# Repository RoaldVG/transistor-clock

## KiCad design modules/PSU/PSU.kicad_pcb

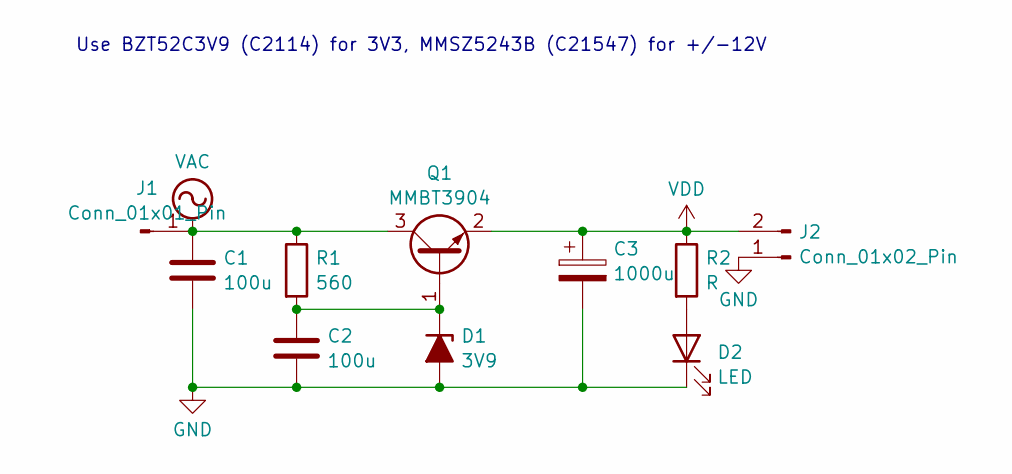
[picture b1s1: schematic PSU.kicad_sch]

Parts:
C1, C2: 100u; CP_EIA-3528-12_Kemet-T; LCSC Part # C16133
C3: 1000u; CP_Elec_10x10.5; LCSC Part # C3359
D1: 3V9; D_SOD-123; LCSC Part # C2114
D2: LED; LED_0603_1608Metric
J1: Conn_01x01_Pin; PinHeader_1x01_P2.54mm_Vertical
J2: Conn_01x02_Pin; PinHeader_1x02_P2.54mm_Vertical
Q1: MMBT3904; SOT-23; LCSC Part # C20526v
R1: 560; R_0603_1608Metric; LCSC Part # C23204
R2: R; R_0603_1608Metric

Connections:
GND: C1.2, C2.1, C3.2, D1.2 (A), D2.1 (K), J2.1
unnamed: C2.2, D1.1 (K), Q1.1 (B), R1.2
unnamed: D2.2 (A), R2.2
VAC: C1.1, J1.1, Q1.3 (C), R1.1
VDD: C3.1, J2.2, Q1.2 (E), R2.1

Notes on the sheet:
Use BZT52C3V9 (C2114) for 3V3, MMSZ5243B (C21547) for +/-12V

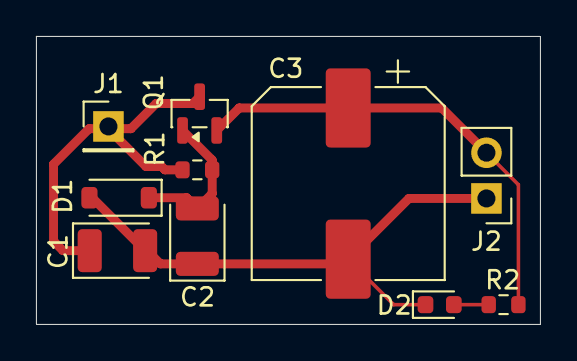
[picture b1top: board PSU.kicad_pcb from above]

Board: 2 copper layers, 28.0 x 16.0 mm, 10 parts (0 on the bottom side), 5 nets.

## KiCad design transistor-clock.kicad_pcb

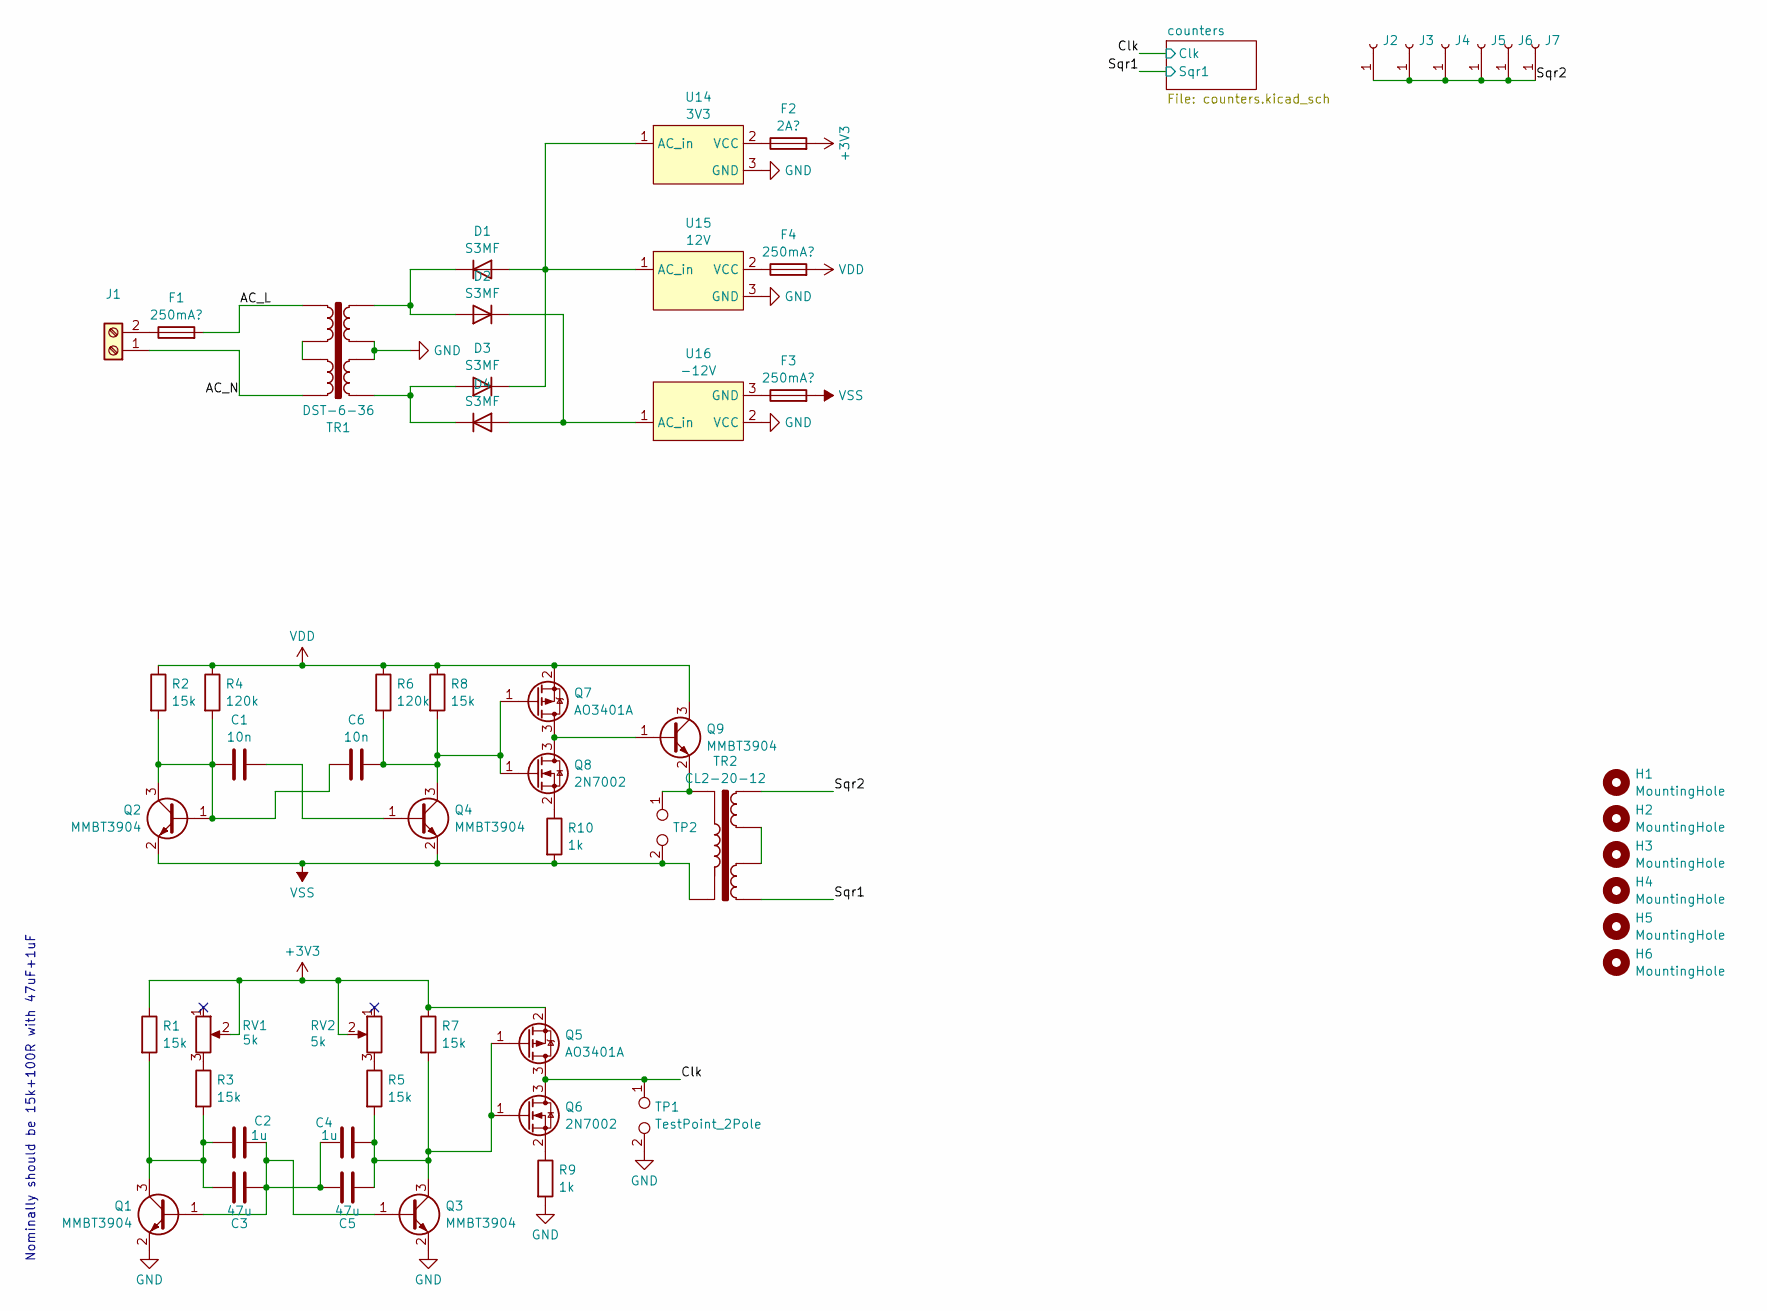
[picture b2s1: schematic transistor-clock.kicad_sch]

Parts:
C1, C6: 10n; C_0603_1608Metric; LCSC Part # C57112
C2, C4: 1u; C_0603_1608Metric; LCSC Part # C15849
C3, C5: 47u; C_0805_2012Metric; LCSC Part # C16780
D1, D2, D3, D4: S3MF; D_SMA; LCSC Part # C64874
F1, F3, F4: 250mA?; Fuse_Littelfuse-NANO2-885; LCSC Part # C41371860
F2: 2A?; Fuse_Littelfuse-NANO2-885; LCSC Part # C41371860
H1, H2, H3, H4, H5, H6: MountingHole; MountingHole_4.3mm_M4_DIN965
J1: Screw_Terminal_01x02; TerminalBlock_MaiXu_MX126-5.0-02P_1x02_P5.00mm
J2, J3, J4, J5, J6, J7: Conn_01x01_Socket; PinHeader_1x01_P2.54mm_Vertical
Q1, Q2, Q3, Q4, Q9: MMBT3904; SOT-23; LCSC Part # C20526v
Q5, Q7: AO3401A; SOT-23; LCSC Part # C15127
Q6, Q8: 2N7002; SOT-23; LCSC Part # C8545
R1, R2, R3, R5, R7, R8: 15k; R_0603_1608Metric; LCSC Part # C22809
R4, R6: 120k; R_0603_1608Metric; LCSC Part # C25808
R9, R10: 1k; R_0603_1608Metric; LCSC Part # C21190
RV1, RV2: 5k; Potentiometer_Bourns_3214J_Horizontal; LCSC Part # C58391
TP1, TP2: TestPoint_2Pole; PinHeader_1x02_P2.54mm_Vertical
TR1: DST-6-36
TR2: CL2-20-12
U14: 3V3; module_PSU
U15: 12V; module_PSU
U16: -12V; module_PSU

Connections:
+3V3: F2.2, Q5.2 (S), R1.1, R7.1, RV1.2, RV2.2; also elsewhere on the board
/AC_L: F1.2, TR1.4
/AC_N: J1.1, TR1.1
/Clk: Q5.3 (D), Q6.3 (D), TP1.1; also elsewhere on the board
/Sqr1: TR2.1; also elsewhere on the board
/Sqr2: J2.1, J3.1, J4.1, J5.1, J6.1, J7.1, TR2.6
GND: Q1.2 (E), Q3.2 (E), R9.2, TP1.2, TR1.6, TR1.7, U14.3 (GND), U15.3 (GND), U16.2 (VCC); also elsewhere on the board
unnamed: D1.2 (A), D3.1 (K), U14.1 (AC_in), U15.1 (AC_in)
unnamed: D1.1 (K), D2.2 (A), TR1.5
unnamed: D2.1 (K), D4.2 (A), U16.1 (AC_in)
unnamed: D3.2 (A), D4.1 (K), TR1.8
unnamed: F1.1, J1.2
unnamed: C2.2, C3.2, C4.1, C5.1, Q1.1 (B), Q3.1 (B)
unnamed: C2.1, C3.1, Q1.3 (C), R1.2, R3.2
unnamed: C1.1, C6.1, Q2.1 (B), Q2.3 (C), R2.2, R4.2
unnamed: C4.2, C5.2, Q3.3 (C), Q5.1 (G), Q6.1 (G), R5.2, R7.2
unnamed: C1.2, Q4.1 (B)
unnamed: C6.2, Q4.3 (C), Q7.1 (G), Q8.1 (G), R6.2, R8.2
unnamed: Q6.2 (S), R9.1
unnamed: Q7.3 (D), Q8.3 (D), Q9.1 (B)
unnamed: Q8.2 (S), R10.1
unnamed: Q9.2 (E), TP2.1, TR2.12
unnamed: R3.1, RV1.3
unnamed: R5.1, RV2.3
unnamed: TR1.2, TR1.3
unnamed: TR2.3, TR2.4
unnamed: F2.1, U14.2 (VCC)
unnamed: F4.1, U15.2 (VCC)
unnamed: F3.1, U16.3 (GND)
VDD: F4.2, Q7.2 (S), Q9.3 (C), R2.1, R4.1, R6.1, R8.1
VSS: F3.2, Q2.2 (E), Q4.2 (E), R10.2, TP2.2, TR2.7

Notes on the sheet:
Nominally should be 15k+100R with 47uF+1uF

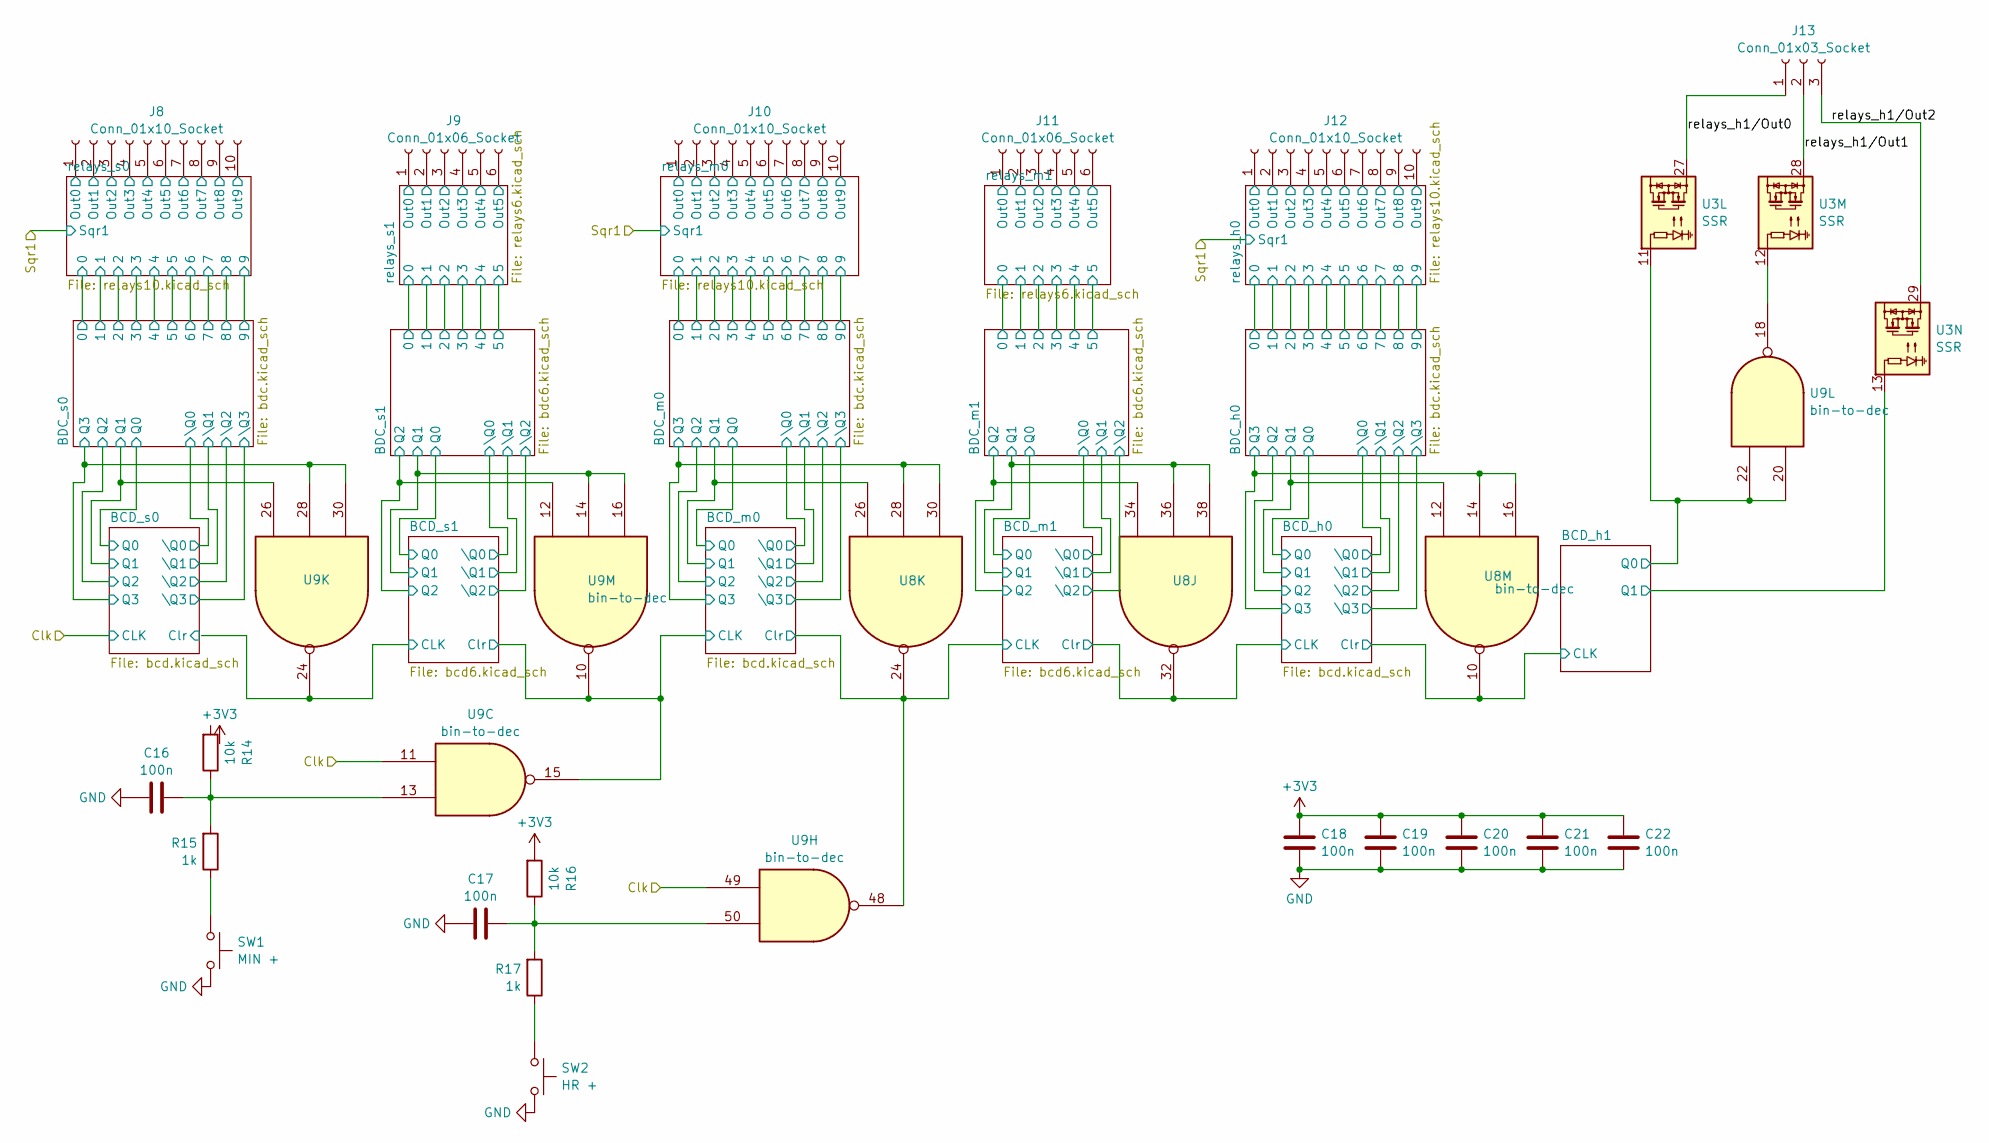
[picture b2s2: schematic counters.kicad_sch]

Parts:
C16, C17, C18, C19, C20, C21, C22: 100n; C_0603_1608Metric; LCSC Part # C14663
J8, J10, J12: Conn_01x10_Socket; PinHeader_1x10_P2.54mm_Vertical
J9, J11: Conn_01x06_Socket; PinHeader_1x06_P2.54mm_Vertical
J13: Conn_01x03_Socket; PinHeader_1x03_P2.54mm_Vertical
R14, R16: 10k; R_0603_1608Metric; LCSC Part # C25804
R15, R17: 1k; R_0603_1608Metric; LCSC Part # C21190
SW1: MIN +; SW_SPST_EVQPE1; LCSC Part # C720477
SW2: HR +; SW_SPST_EVQPE1; LCSC Part # C720477
U3: SSR; module_ssr
U8, U9: bin-to-dec; module_bdc_mpcie; LCSC Part # C185937

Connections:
+3V3: C18.1, C19.1, C20.1, C21.1, C22.1, R16.2, U8.24, U8.32, U9.10, U9.15, U9.24, U9.48; also elsewhere on the board
/Clk: U9.11, U9.49; also elsewhere on the board
/counters/BCD_h0/Clr: U8.10; also elsewhere on the board
/counters/BCD_h0/Q1: U8.12; also elsewhere on the board
/counters/BCD_h0/Q3: U8.14, U8.16; also elsewhere on the board
/counters/BCD_h1/Clr: U3.13; also elsewhere on the board
/counters/BCD_h1/Q0: U3.11, U9.20, U9.22; also elsewhere on the board
/counters/BCD_m0/Q1: U8.26; also elsewhere on the board
/counters/BCD_m0/Q3: U8.28, U8.30; also elsewhere on the board
/counters/BCD_m1/Q1: U8.36, U8.38; also elsewhere on the board
/counters/BCD_m1/Q2: U8.34; also elsewhere on the board
/counters/BCD_s0/Q1: U9.26; also elsewhere on the board
/counters/BCD_s0/Q3: U9.28, U9.30; also elsewhere on the board
/counters/BCD_s1/Q1: U9.14, U9.16; also elsewhere on the board
/counters/BCD_s1/Q2: U9.12; also elsewhere on the board
/counters/relays_h0/Out0: J12.1; also elsewhere on the board
/counters/relays_h0/Out1: J12.2; also elsewhere on the board
/counters/relays_h0/Out2: J12.3; also elsewhere on the board
/counters/relays_h0/Out3: J12.4; also elsewhere on the board
/counters/relays_h0/Out4: J12.5; also elsewhere on the board
/counters/relays_h0/Out5: J12.6; also elsewhere on the board
/counters/relays_h0/Out6: J12.7; also elsewhere on the board
/counters/relays_h0/Out7: J12.8; also elsewhere on the board
/counters/relays_h0/Out8: J12.9; also elsewhere on the board
/counters/relays_h0/Out9: J12.10; also elsewhere on the board
/counters/relays_h1/Out0: J13.1, U3.27
/counters/relays_h1/Out1: J13.2, U3.28
/counters/relays_h1/Out2: J13.3, U3.29
/counters/relays_m0/Out0: J10.1; also elsewhere on the board
/counters/relays_m0/Out1: J10.2; also elsewhere on the board
/counters/relays_m0/Out2: J10.3; also elsewhere on the board
/counters/relays_m0/Out3: J10.4; also elsewhere on the board
/counters/relays_m0/Out4: J10.5; also elsewhere on the board
/counters/relays_m0/Out5: J10.6; also elsewhere on the board
/counters/relays_m0/Out6: J10.7; also elsewhere on the board
/counters/relays_m0/Out7: J10.8; also elsewhere on the board
/counters/relays_m0/Out8: J10.9; also elsewhere on the board
/counters/relays_m0/Out9: J10.10; also elsewhere on the board
/counters/relays_m1/Out0: J11.1; also elsewhere on the board
/counters/relays_m1/Out1: J11.2; also elsewhere on the board
/counters/relays_m1/Out2: J11.3; also elsewhere on the board
/counters/relays_m1/Out3: J11.4; also elsewhere on the board
/counters/relays_m1/Out4: J11.5; also elsewhere on the board
/counters/relays_m1/Out5: J11.6; also elsewhere on the board
/counters/relays_s0/Out0: J8.1; also elsewhere on the board
/counters/relays_s0/Out1: J8.2; also elsewhere on the board
/counters/relays_s0/Out2: J8.3; also elsewhere on the board
/counters/relays_s0/Out3: J8.4; also elsewhere on the board
/counters/relays_s0/Out4: J8.5; also elsewhere on the board
/counters/relays_s0/Out5: J8.6; also elsewhere on the board
/counters/relays_s0/Out6: J8.7; also elsewhere on the board
/counters/relays_s0/Out7: J8.8; also elsewhere on the board
/counters/relays_s0/Out8: J8.9; also elsewhere on the board
/counters/relays_s0/Out9: J8.10; also elsewhere on the board
/counters/relays_s1/Out0: J9.1; also elsewhere on the board
/counters/relays_s1/Out1: J9.2; also elsewhere on the board
/counters/relays_s1/Out2: J9.3; also elsewhere on the board
/counters/relays_s1/Out3: J9.4; also elsewhere on the board
/counters/relays_s1/Out4: J9.5; also elsewhere on the board
/counters/relays_s1/Out5: J9.6; also elsewhere on the board
GND: C16.2, C17.2, C18.2, C19.2, C20.2, C21.2, C22.2, SW1.1, SW2.1; also elsewhere on the board
unnamed: C16.1, R14.1, R15.2, U9.13
unnamed: C17.1, R16.1, R17.2, U9.50
unnamed: R15.1, SW1.2
unnamed: R17.1, SW2.2
unnamed: U3.12, U9.18

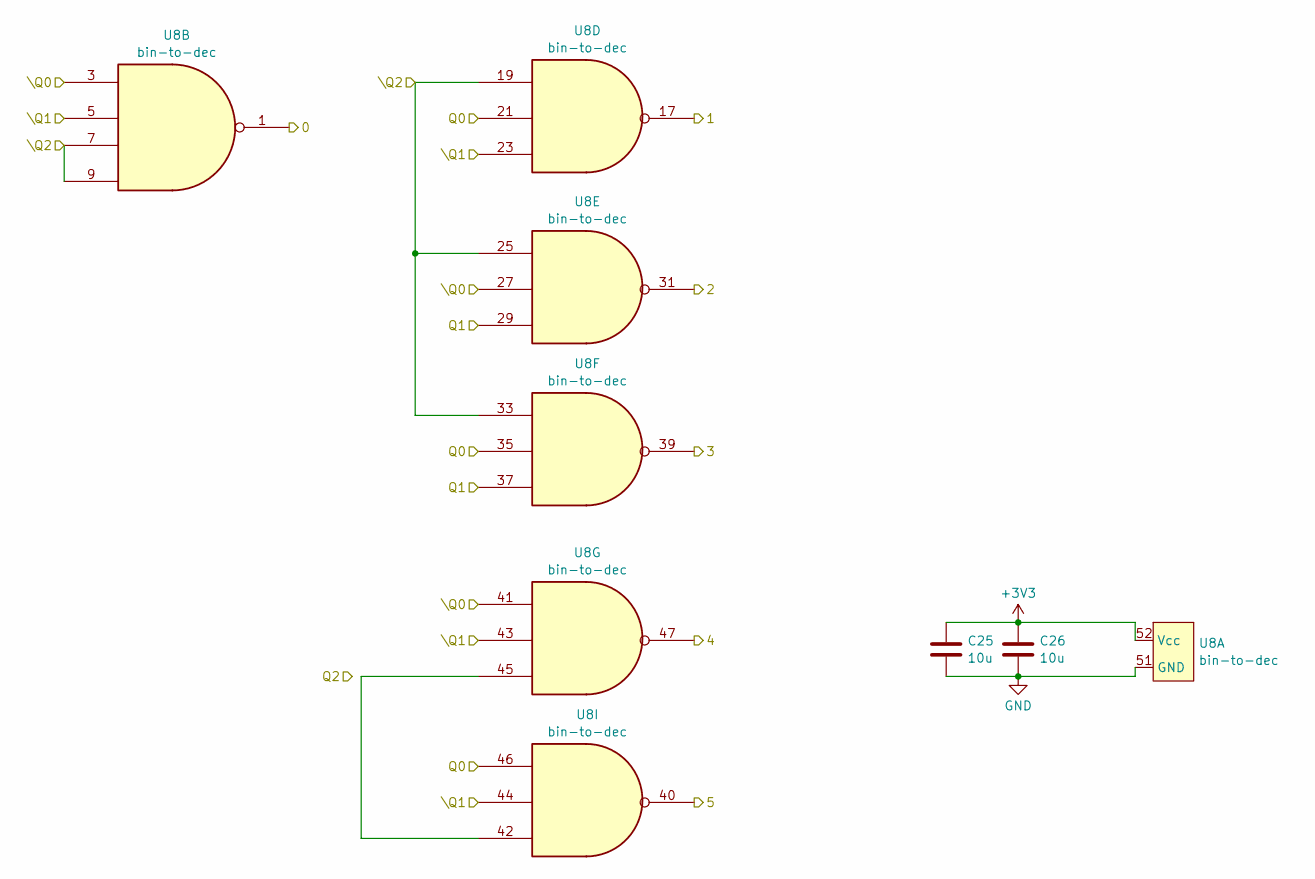
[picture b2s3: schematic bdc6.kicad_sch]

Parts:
C25, C26: 10u; C_0603_1608Metric; LCSC Part # C19702
U8: bin-to-dec; module_bdc_mpcie; LCSC Part # C185937

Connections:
+3V3: C25.1, C26.1, U8.52 (Vcc); also elsewhere on the board
/counters/BCD_m1/Q0: U8.21, U8.35, U8.46; also elsewhere on the board
/counters/BCD_m1/Q1: U8.29, U8.37; also elsewhere on the board
/counters/BCD_m1/\Q0: U8.3, U8.27, U8.41; also elsewhere on the board
/counters/BCD_m1/\Q1: U8.5, U8.23, U8.43, U8.44; also elsewhere on the board
/counters/BCD_m1/\Q2: U8.7, U8.9, U8.19, U8.25, U8.33; also elsewhere on the board
/counters/BDC_m1/0: U8.1; also elsewhere on the board
/counters/BDC_m1/1: U8.17; also elsewhere on the board
/counters/BDC_m1/2: U8.31; also elsewhere on the board
/counters/BDC_m1/3: U8.39; also elsewhere on the board
/counters/BDC_m1/4: U8.47; also elsewhere on the board
/counters/BDC_m1/5: U8.40; also elsewhere on the board
GND: C25.2, C26.2, U8.51 (GND); also elsewhere on the board
unnamed: U8.42, U8.45

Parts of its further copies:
C31, C32: 10u; C_0603_1608Metric; LCSC Part # C19702

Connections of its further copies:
+3V3: C31.1, C32.1; also elsewhere on the board
GND: C31.2, C32.2; also elsewhere on the board

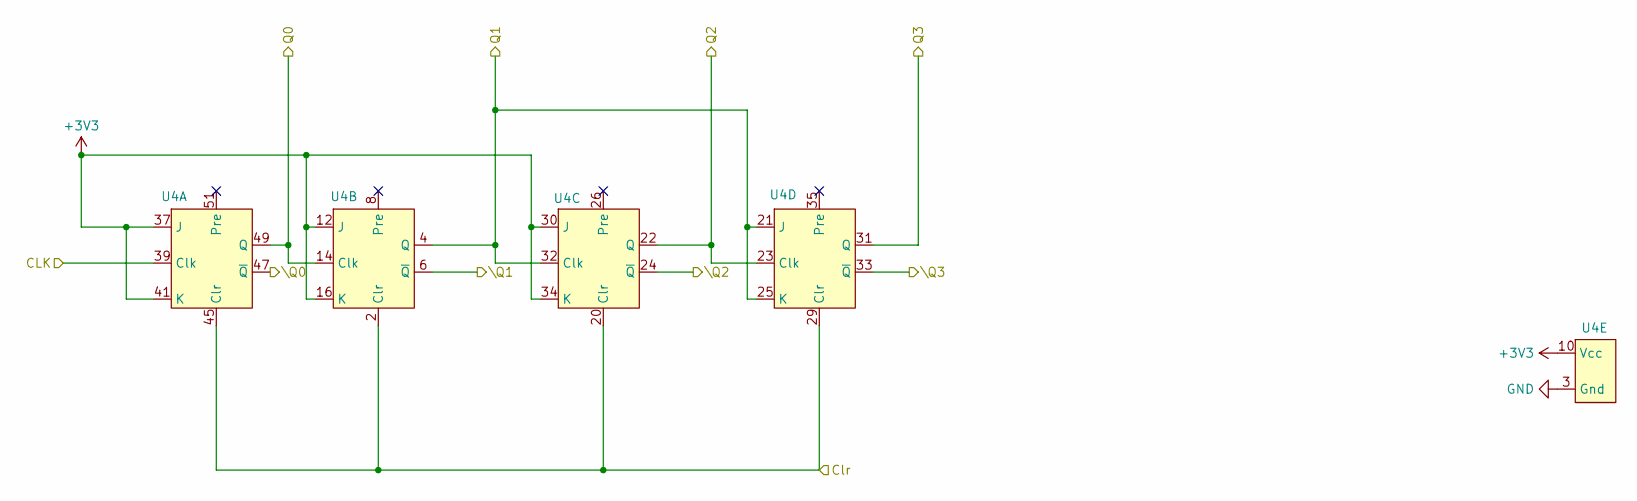
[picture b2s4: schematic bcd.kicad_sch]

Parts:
U4: flipflop; module_flipflop_mpcie; LCSC Part # C185937

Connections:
+3V3: U4.10 (Vcc), U4.12 (J), U4.16 (K), U4.18 (Vcc), U4.28 (Vcc), U4.30 (J), U4.34 (K), U4.36 (Vcc), U4.37 (J), U4.39 (Clk), U4.41 (K), U4.46 (Vcc); also elsewhere on the board
/counters/BCD_h0/Clr: U4.2 (Clr), U4.20 (Clr), U4.29 (Clr), U4.45 (Clr); also elsewhere on the board
/counters/BCD_h0/Q0: U4.14 (Clk), U4.49 (Q); also elsewhere on the board
/counters/BCD_h0/Q1: U4.4 (Q), U4.21 (J), U4.25 (K), U4.32 (Clk); also elsewhere on the board
/counters/BCD_h0/Q2: U4.22 (Q), U4.23 (Clk); also elsewhere on the board
/counters/BCD_h0/Q3: U4.31 (Q); also elsewhere on the board
/counters/BCD_h0/\Q0: U4.47 (~Q); also elsewhere on the board
/counters/BCD_h0/\Q1: U4.6 (~Q); also elsewhere on the board
/counters/BCD_h0/\Q2: U4.24 (~Q); also elsewhere on the board
/counters/BCD_h0/\Q3: U4.33 (~Q); also elsewhere on the board
GND: U4.3 (Gnd), U4.9 (Gnd), U4.19 (Gnd), U4.27 (Gnd), U4.43 (Gnd); also elsewhere on the board

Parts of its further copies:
U7, U10: flipflop; module_flipflop_mpcie; LCSC Part # C185937

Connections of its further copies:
+3V3: U7.10 (Vcc), U7.12 (J), U7.16 (K), U7.18 (Vcc), U7.28 (Vcc), U7.30 (J), U7.34 (K), U7.36 (Vcc), U7.37 (J), U7.41 (K), U7.46 (Vcc), U10.2 (Clr), U10.10 (Vcc), U10.12 (J), U10.16 (K), U10.18 (Vcc), U10.20 (Clr), U10.28 (Vcc), U10.29 (Clr), U10.30 (J), U10.34 (K), U10.36 (Vcc), U10.37 (J), U10.39 (Clk), U10.41 (K), U10.45 (Clr), U10.46 (Vcc); also elsewhere on the board
/Clk: U7.39 (Clk); also elsewhere on the board
/counters/BCD_m0/Q0: U10.14 (Clk), U10.49 (Q); also elsewhere on the board
/counters/BCD_m0/Q1: U10.4 (Q), U10.21 (J), U10.25 (K), U10.32 (Clk); also elsewhere on the board
/counters/BCD_m0/Q2: U10.22 (Q), U10.23 (Clk); also elsewhere on the board
/counters/BCD_m0/Q3: U10.31 (Q); also elsewhere on the board
/counters/BCD_m0/\Q0: U10.47 (~Q); also elsewhere on the board
/counters/BCD_m0/\Q1: U10.6 (~Q); also elsewhere on the board
/counters/BCD_m0/\Q2: U10.24 (~Q); also elsewhere on the board
/counters/BCD_m0/\Q3: U10.33 (~Q); also elsewhere on the board
/counters/BCD_s0/Clr: U7.2 (Clr), U7.20 (Clr), U7.29 (Clr), U7.45 (Clr)
/counters/BCD_s0/Q0: U7.14 (Clk), U7.49 (Q); also elsewhere on the board
/counters/BCD_s0/Q1: U7.4 (Q), U7.21 (J), U7.25 (K), U7.32 (Clk); also elsewhere on the board
/counters/BCD_s0/Q2: U7.22 (Q), U7.23 (Clk); also elsewhere on the board
/counters/BCD_s0/Q3: U7.31 (Q); also elsewhere on the board
/counters/BCD_s0/\Q0: U7.47 (~Q); also elsewhere on the board
/counters/BCD_s0/\Q1: U7.6 (~Q); also elsewhere on the board
/counters/BCD_s0/\Q2: U7.24 (~Q); also elsewhere on the board
/counters/BCD_s0/\Q3: U7.33 (~Q); also elsewhere on the board
GND: U7.3 (Gnd), U7.9 (Gnd), U7.19 (Gnd), U7.27 (Gnd), U7.43 (Gnd), U10.3 (Gnd), U10.9 (Gnd), U10.19 (Gnd), U10.27 (Gnd), U10.43 (Gnd); also elsewhere on the board

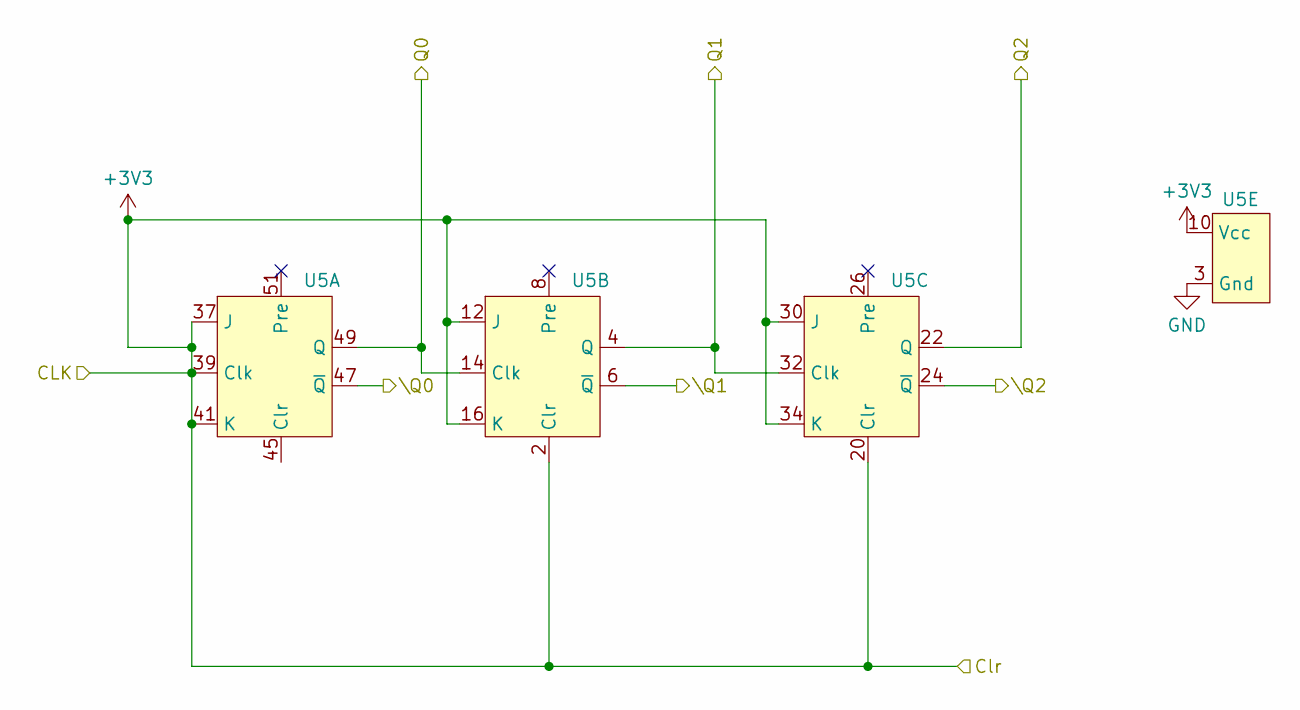
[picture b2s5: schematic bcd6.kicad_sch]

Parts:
U5: flipflop; module_flipflop_mpcie; LCSC Part # C185937

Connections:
+3V3: U5.2 (Clr), U5.10 (Vcc), U5.12 (J), U5.16 (K), U5.18 (Vcc), U5.20 (Clr), U5.28 (Vcc), U5.30 (J), U5.34 (K), U5.36 (Vcc), U5.37 (J), U5.39 (Clk), U5.41 (K), U5.46 (Vcc); also elsewhere on the board
/counters/BCD_s1/Q0: U5.14 (Clk), U5.49 (Q); also elsewhere on the board
/counters/BCD_s1/Q1: U5.4 (Q), U5.32 (Clk); also elsewhere on the board
/counters/BCD_s1/Q2: U5.22 (Q); also elsewhere on the board
/counters/BCD_s1/\Q0: U5.47 (~Q); also elsewhere on the board
/counters/BCD_s1/\Q1: U5.6 (~Q); also elsewhere on the board
/counters/BCD_s1/\Q2: U5.24 (~Q); also elsewhere on the board
GND: U5.3 (Gnd), U5.9 (Gnd), U5.19 (Gnd), U5.27 (Gnd), U5.43 (Gnd); also elsewhere on the board

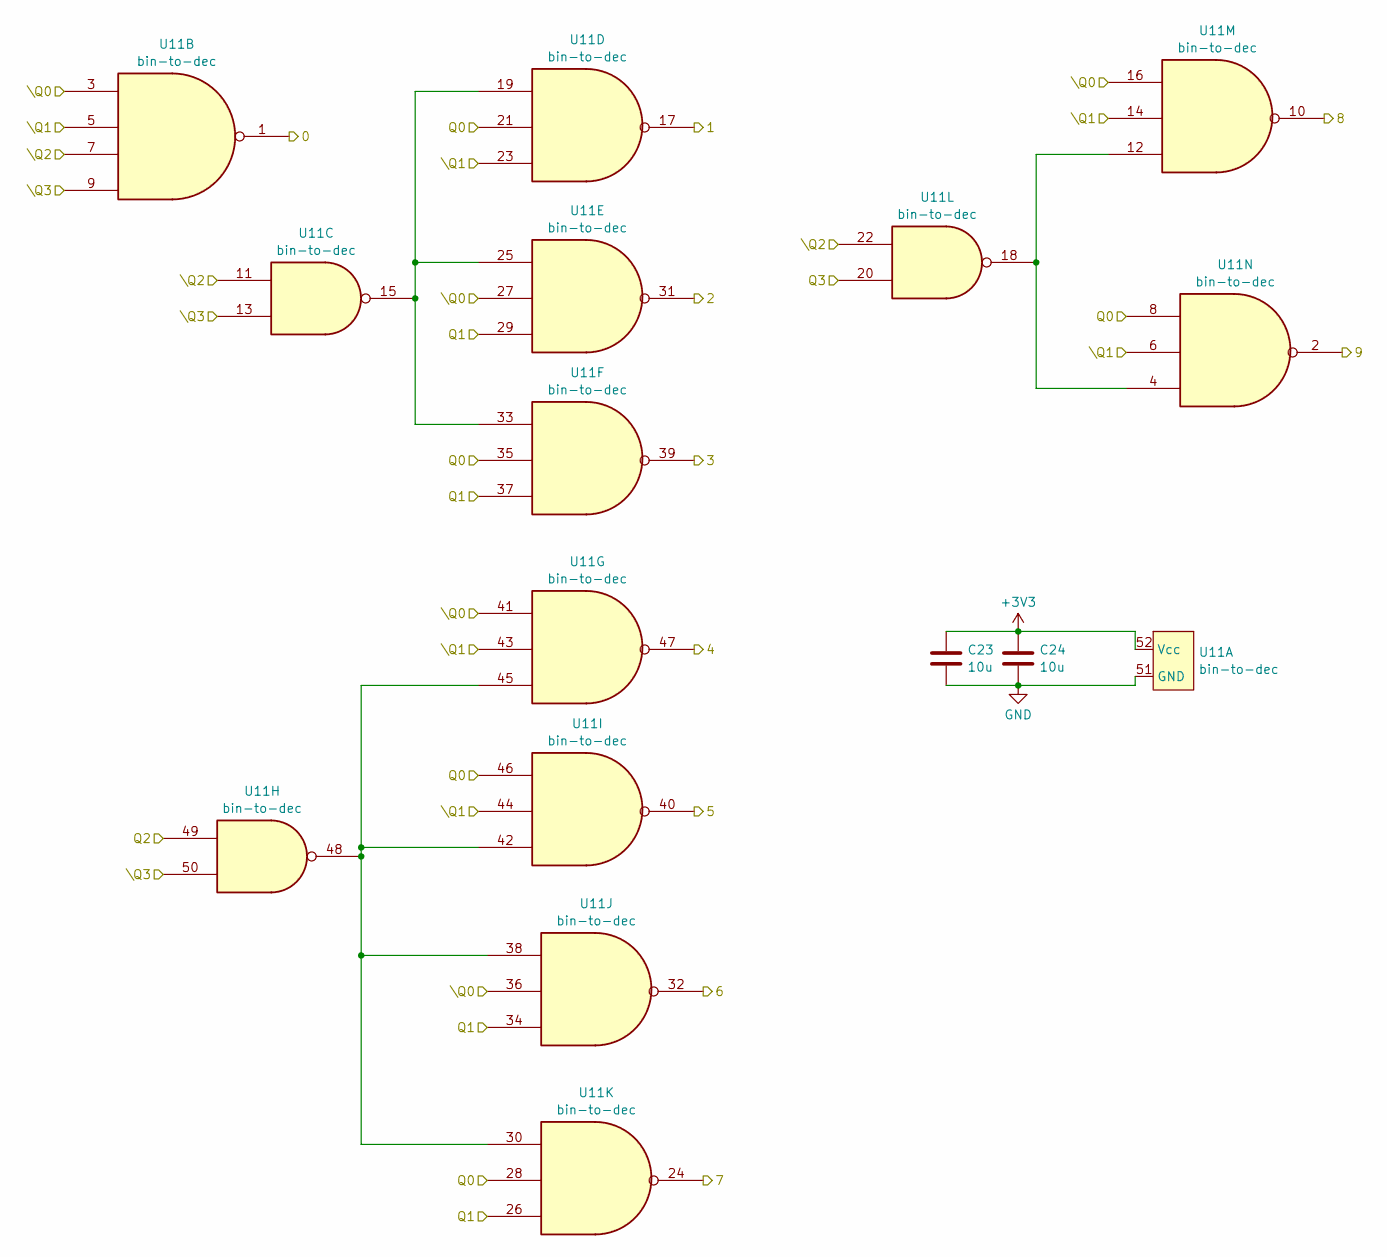
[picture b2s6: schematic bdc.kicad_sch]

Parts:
C23, C24: 10u; C_0603_1608Metric; LCSC Part # C19702
U11: bin-to-dec; module_bdc_mpcie; LCSC Part # C185937

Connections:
+3V3: C23.1, C24.1, U11.52 (Vcc); also elsewhere on the board
/counters/BCD_m0/Q0: U11.8, U11.21, U11.28, U11.35, U11.46; also elsewhere on the board
/counters/BCD_m0/Q1: U11.26, U11.29, U11.34, U11.37; also elsewhere on the board
/counters/BCD_m0/Q2: U11.49; also elsewhere on the board
/counters/BCD_m0/Q3: U11.20; also elsewhere on the board
/counters/BCD_m0/\Q0: U11.3, U11.16, U11.27, U11.36, U11.41; also elsewhere on the board
/counters/BCD_m0/\Q1: U11.5, U11.6, U11.14, U11.23, U11.43, U11.44; also elsewhere on the board
/counters/BCD_m0/\Q2: U11.7, U11.11, U11.22; also elsewhere on the board
/counters/BCD_m0/\Q3: U11.9, U11.13, U11.50; also elsewhere on the board
/counters/BDC_m0/0: U11.1; also elsewhere on the board
/counters/BDC_m0/1: U11.17; also elsewhere on the board
/counters/BDC_m0/2: U11.31; also elsewhere on the board
/counters/BDC_m0/3: U11.39; also elsewhere on the board
/counters/BDC_m0/4: U11.47; also elsewhere on the board
/counters/BDC_m0/5: U11.40; also elsewhere on the board
/counters/BDC_m0/6: U11.32; also elsewhere on the board
/counters/BDC_m0/7: U11.24; also elsewhere on the board
/counters/BDC_m0/8: U11.10; also elsewhere on the board
/counters/BDC_m0/9: U11.2; also elsewhere on the board
GND: C23.2, C24.2, U11.51 (GND); also elsewhere on the board
unnamed: U11.4, U11.12, U11.18
unnamed: U11.15, U11.19, U11.25, U11.33
unnamed: U11.30, U11.38, U11.42, U11.45, U11.48

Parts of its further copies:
C27, C28, C29, C30: 10u; C_0603_1608Metric; LCSC Part # C19702
U12, U13: bin-to-dec; module_bdc_mpcie; LCSC Part # C185937

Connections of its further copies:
+3V3: C27.1, C28.1, C29.1, C30.1, U12.52 (Vcc), U13.52 (Vcc); also elsewhere on the board
/counters/BCD_h0/Q0: U12.8, U12.21, U12.28, U12.35, U12.46; also elsewhere on the board
/counters/BCD_h0/Q1: U12.26, U12.29, U12.34, U12.37; also elsewhere on the board
/counters/BCD_h0/Q2: U12.49; also elsewhere on the board
/counters/BCD_h0/Q3: U12.20; also elsewhere on the board
/counters/BCD_h0/\Q0: U12.3, U12.16, U12.27, U12.36, U12.41; also elsewhere on the board
/counters/BCD_h0/\Q1: U12.5, U12.6, U12.14, U12.23, U12.43, U12.44; also elsewhere on the board
/counters/BCD_h0/\Q2: U12.7, U12.11, U12.22; also elsewhere on the board
/counters/BCD_h0/\Q3: U12.9, U12.13, U12.50; also elsewhere on the board
/counters/BCD_s0/Q0: U13.8, U13.21, U13.28, U13.35, U13.46; also elsewhere on the board
/counters/BCD_s0/Q1: U13.26, U13.29, U13.34, U13.37; also elsewhere on the board
/counters/BCD_s0/Q2: U13.49; also elsewhere on the board
/counters/BCD_s0/Q3: U13.20; also elsewhere on the board
/counters/BCD_s0/\Q0: U13.3, U13.16, U13.27, U13.36, U13.41; also elsewhere on the board
/counters/BCD_s0/\Q1: U13.5, U13.6, U13.14, U13.23, U13.43, U13.44; also elsewhere on the board
/counters/BCD_s0/\Q2: U13.7, U13.11, U13.22; also elsewhere on the board
/counters/BCD_s0/\Q3: U13.9, U13.13, U13.50; also elsewhere on the board
/counters/BDC_h0/0: U12.1; also elsewhere on the board
/counters/BDC_h0/1: U12.17; also elsewhere on the board
/counters/BDC_h0/2: U12.31; also elsewhere on the board
/counters/BDC_h0/3: U12.39; also elsewhere on the board
/counters/BDC_h0/4: U12.47; also elsewhere on the board
/counters/BDC_h0/5: U12.40; also elsewhere on the board
/counters/BDC_h0/6: U12.32; also elsewhere on the board
/counters/BDC_h0/7: U12.24; also elsewhere on the board
/counters/BDC_h0/8: U12.10; also elsewhere on the board
/counters/BDC_h0/9: U12.2; also elsewhere on the board
/counters/BDC_s0/0: U13.1; also elsewhere on the board
/counters/BDC_s0/1: U13.17; also elsewhere on the board
/counters/BDC_s0/2: U13.31; also elsewhere on the board
/counters/BDC_s0/3: U13.39; also elsewhere on the board
/counters/BDC_s0/4: U13.47; also elsewhere on the board
/counters/BDC_s0/5: U13.40; also elsewhere on the board
/counters/BDC_s0/6: U13.32; also elsewhere on the board
/counters/BDC_s0/7: U13.24; also elsewhere on the board
/counters/BDC_s0/8: U13.10; also elsewhere on the board
/counters/BDC_s0/9: U13.2; also elsewhere on the board
GND: C27.2, C28.2, C29.2, C30.2, U12.51 (GND), U13.51 (GND); also elsewhere on the board
unnamed: U12.4, U12.12, U12.18
unnamed: U12.15, U12.19, U12.25, U12.33
unnamed: U12.30, U12.38, U12.42, U12.45, U12.48
unnamed: U13.4, U13.12, U13.18
unnamed: U13.15, U13.19, U13.25, U13.33
unnamed: U13.30, U13.38, U13.42, U13.45, U13.48

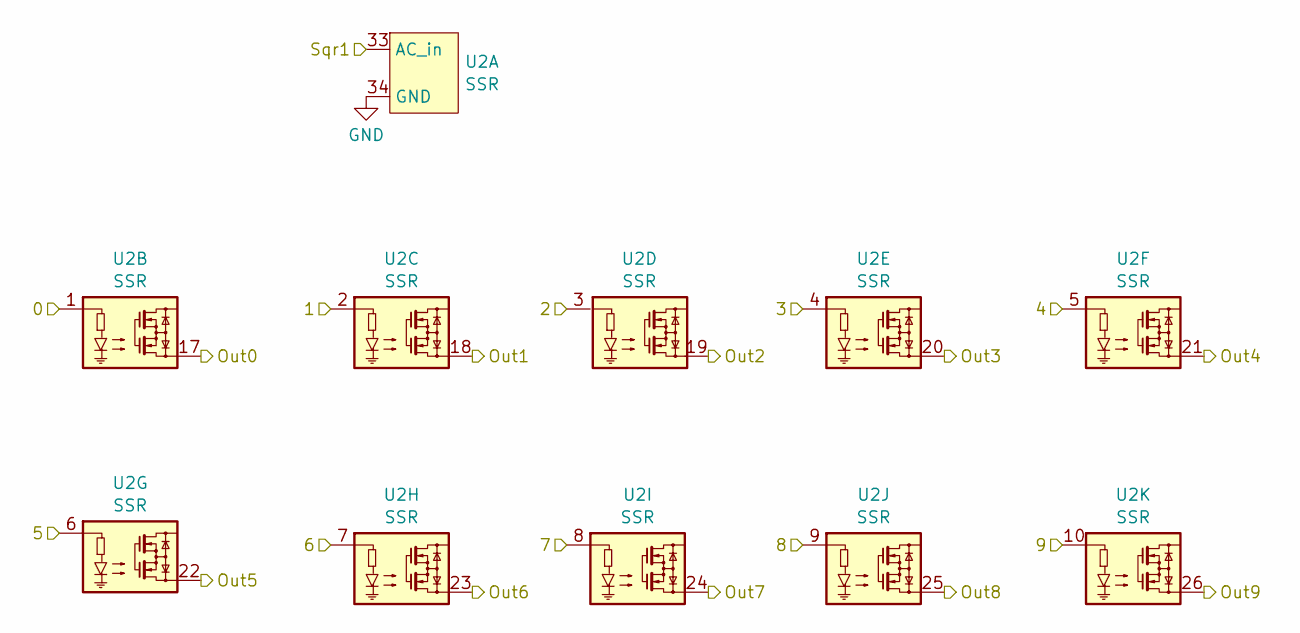
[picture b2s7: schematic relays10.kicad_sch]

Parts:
U2: SSR; module_ssr

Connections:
/Sqr1: U2.33 (AC_in); also elsewhere on the board
/counters/BDC_m0/0: U2.1; also elsewhere on the board
/counters/BDC_m0/1: U2.2; also elsewhere on the board
/counters/BDC_m0/2: U2.3; also elsewhere on the board
/counters/BDC_m0/3: U2.4; also elsewhere on the board
/counters/BDC_m0/4: U2.5; also elsewhere on the board
/counters/BDC_m0/5: U2.6; also elsewhere on the board
/counters/BDC_m0/6: U2.7; also elsewhere on the board
/counters/BDC_m0/7: U2.8; also elsewhere on the board
/counters/BDC_m0/8: U2.9; also elsewhere on the board
/counters/BDC_m0/9: U2.10; also elsewhere on the board
/counters/relays_m0/Out0: U2.17; also elsewhere on the board
/counters/relays_m0/Out1: U2.18; also elsewhere on the board
/counters/relays_m0/Out2: U2.19; also elsewhere on the board
/counters/relays_m0/Out3: U2.20; also elsewhere on the board
/counters/relays_m0/Out4: U2.21; also elsewhere on the board
/counters/relays_m0/Out5: U2.22; also elsewhere on the board
/counters/relays_m0/Out6: U2.23; also elsewhere on the board
/counters/relays_m0/Out7: U2.24; also elsewhere on the board
/counters/relays_m0/Out8: U2.25; also elsewhere on the board
/counters/relays_m0/Out9: U2.26; also elsewhere on the board
GND: U2.34 (GND); also elsewhere on the board

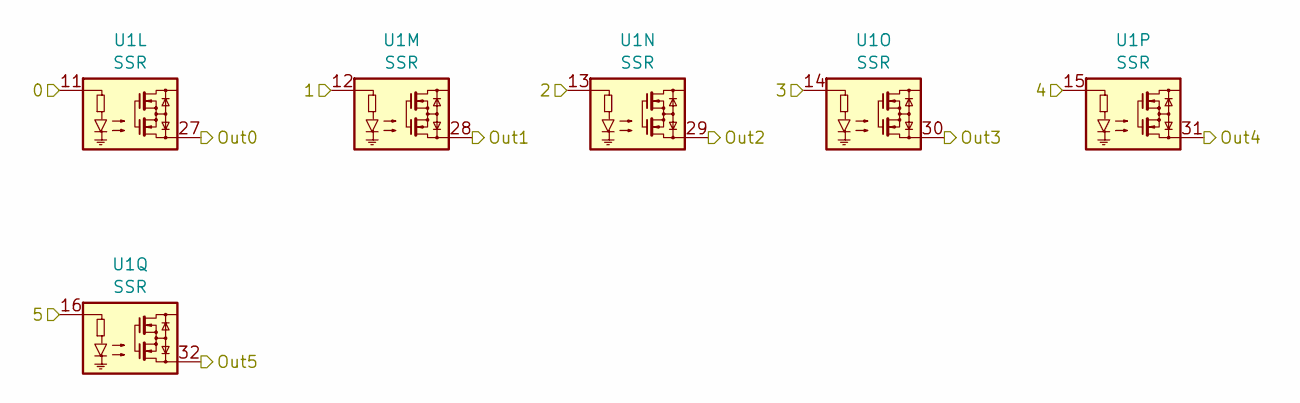
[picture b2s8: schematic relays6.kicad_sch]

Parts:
U1: SSR; module_ssr

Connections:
/counters/BDC_s1/0: U1.11; also elsewhere on the board
/counters/BDC_s1/1: U1.12; also elsewhere on the board
/counters/BDC_s1/2: U1.13; also elsewhere on the board
/counters/BDC_s1/3: U1.14; also elsewhere on the board
/counters/BDC_s1/4: U1.15; also elsewhere on the board
/counters/BDC_s1/5: U1.16; also elsewhere on the board
/counters/relays_s1/Out0: U1.27; also elsewhere on the board
/counters/relays_s1/Out1: U1.28; also elsewhere on the board
/counters/relays_s1/Out2: U1.29; also elsewhere on the board
/counters/relays_s1/Out3: U1.30; also elsewhere on the board
/counters/relays_s1/Out4: U1.31; also elsewhere on the board
/counters/relays_s1/Out5: U1.32; also elsewhere on the board
